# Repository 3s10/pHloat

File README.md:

# pHloat pH Monitoring System

A complete ESP32-based pH monitoring system for brewery fermentation, designed to work alongside Tilt Hydrometers and integrate with Google Sheets.

## System Overview

The pHloat system consists of two components:

1. **pHloat pH Sensor** (ESP32-S3) - Battery-powered sensor that reads pH every minute
2. **pHloat Relay** (ESP32) - Central hub that receives data, calibrates sensors, and uploads to Google Sheets

## Features

- ✅ 1-minute reading intervals with deep sleep for battery efficiency
- ✅ ESP-NOW wireless communication (no WiFi needed for sensors)
- ✅ Web-based configuration and calibration
- ✅ 3-point pH calibration (pH 4, 7, 10)
- ✅ Multiple sensor support (up to 10 sensors)
- ✅ Google Sheets integration with Tilt data matching
- ✅ Local data storage with download capability
- ✅ Storage management with alerts
- ✅ Real-time NTP time synchronization

## Hardware Requirements

### pHloat pH Sensor (per sensor)
- ESP32-S3 development board
- Atlas Scientific pH OEM Circuit (I²C mode)
- Atlas Scientific pH probe
- BNC connector
- Battery (LiPo 3.7V recommended, 2000mAh+ for ~60 days)
- Battery charging circuit (optional but recommended)
- Waterproof enclosure

### pHloat Relay (one per brewery)
- ESP32 development board (any variant)
- USB power supply (always-on)
- Optional: SD card module for extended storage

## Wiring Diagrams

### pH Sensor Wiring

```
ESP32-S3              Atlas Scientific pH OEM
=========             =======================
GPIO 8 (SDA)  ------>  SDA
GPIO 9 (SCL)  ------>  SCL
3.3V          ------>  VCC
GND           ------>  GND

Atlas Scientific pH OEM    pH Probe
========================   =========
PRB (BNC connector) -----> pH Probe (BNC)
```

**Important Notes:**
- The Atlas Scientific pH OEM operates at 3.3V (perfect for ESP32)
- Use I²C mode (default on pH OEM)
- Keep I²C wires as short as possible for reliability
- The pH probe MUST be kept hydrated - store in storage solution when not in use

### Power Considerations

**pH Sensor (Battery-Powered):**
- Deep sleep current: ~10µA
- Active current: ~50mA for ~1 second
- Average: ~0.8mA
- 2000mAh battery = ~104 days runtime (1 reading/minute)

**Relay (Wall-Powered):**
- Continuous operation via USB
- Current draw: ~150mA

## Software Setup

### 1. Arduino IDE Configuration

1. Install Arduino IDE (version 2.0+)
2. Add ESP32 board support:
   - Go to File → Preferences
   - Add to "Additional Board Manager URLs": 
     ```
     https://raw.githubusercontent.com/espressif/arduino-esp32/gh-pages/package_esp32_index.json
     ```
   - Go to Tools → Board → Board Manager
   - Search for "esp32" and install "esp32 by Espressif Systems"

3. Install required libraries:
   - Open Arduino IDE
   - Go to Tools → Manage Libraries
   - Search and install:
     - **ArduinoJson** by Benoit Blanchon (version 6.21.0 or higher)
     - This is required for JSON parsing in the web interface
   
4. IMPORTANT - Atlas Scientific I2C Communication:
   - The code uses direct I2C Wire library commands
   - No separate Atlas library needed
   - Commands are sent via Wire.write() following Atlas protocol

### 2. Upload pH Sensor Sketch

1. Open `pHloat_Sensor/pHloat_Sensor.ino`
2. Select board: Tools → Board → ESP32S3 Dev Module
3. Configure board settings:
   - USB CDC On Boot: Enabled
   - Flash Size: 4MB (or your board's size)
   - Partition Scheme: Default
4. Connect ESP32-S3 via USB
5. Select correct COM port
6. Click Upload

### 3. Upload Relay Sketch

1. Open `pHloat_Relay/pHloat_Relay.ino`
2. **IMPORTANT:** Make sure `pHloat_Relay_WebUI.ino` is in the same folder
3. Select board: Tools → Board → ESP32 Dev Module (or your specific board)
4. Connect ESP32 via USB
5. Select correct COM port
6. Click Upload

### 4. Initial Configuration

#### Configure pH Sensor:

1. Power on the pH sensor while holding the BOOT button (GPIO 0)
2. Connect to WiFi network: `pHloat-XXXXXXXX`
3. Password: check Serial Monitor — a random 16-character password is generated on first boot
4. Open browser to `192.168.4.1`
5. Enter:
   - Device name (e.g., "Fermenter-1")
   - Relay MAC address (get this from relay serial monitor)
6. Save - sensor will reboot and start taking readings

#### Configure Relay:

1. Power on relay
2. Note the MAC address printed in Serial Monitor
3. If WiFi not configured, connect to `pHloat-Relay` AP (password printed to Serial Monitor on first boot)
4. Open browser to `192.168.4.1` (or relay's IP if WiFi configured)
5. Go to Configuration page
6. Enter:
   - WiFi SSID and password
   - NTP server (default: pool.ntp.org)
   - Timezone offset in seconds (e.g., -18000 for EST)
   - Google Sheets URL (optional, see below)
7. Save - relay will reboot and connect to WiFi

## Google Sheets Integration

The relay uses one upload path for **both** Google Apps Script and Tilt Pi. See `integration/UPLOAD_API.md` for the shared JSON contract.

You have **two destination options** for remote upload:

### Option 1: Direct Upload (pHloat Relay → Google Sheets)

Each pHloat Relay uploads directly to Google Sheets using Google Apps Script.

**Pros:**
- Simple setup
- Works anywhere with WiFi
- No additional hardware

**Cons:**
- Each relay needs Google Sheets configured
- Multiple relays = multiple configurations

**Setup:** See "Setup Google Apps Script" section below

### Option 2: Tilt Pi Integration (Recommended for Tilt Users)

If you already have a Raspberry Pi running Tilt Pi, use it as a central hub!

**Pros:**
- ✅ Central hub for both Tilt and pHloat data
- ✅ Better timestamp matching (direct database access)
- ✅ Unified dashboard
- ✅ One Google Sheets configuration
- ✅ Lower power (relays can be eliminated)

**Cons:**
- Requires Raspberry Pi
- Slightly more complex initial setup

**Setup:** See **TILT_PI_INTEGRATION.md** for complete instructions

---

## Setup Google Apps Script (Option 1 - Direct Upload)

1. Create a new Google Sheet for your fermentation data
2. Go to Extensions → Apps Script
3. Delete any existing code
4. Copy and paste the contents of `GoogleAppsScript.js`
5. Save the project (name it "pHloat Logger")
6. Click "Deploy" → "New deployment"
7. Settings:
   - Type: Web app
   - Execute as: Me
   - Who has access: Anyone
8. Click "Deploy"
9. Copy the Web App URL
10. In Apps Script: Project Settings → Script properties → add `PHLOAT_UPLOAD_SECRET` (generate a long random string)
11. Paste the Web App URL into the pHloat Relay configuration
12. Set the same upload token in the Relay **Upload Token** field (or leave blank to reuse the API key)

All relay HTTPS uploads send `X-pHloat-Token` — requests without a matching token are rejected.

### Tilt Integration:

The Google Apps Script automatically searches for Tilt data sheets and matches pH readings by timestamp (±1 minute). 

**Expected Tilt sheet format:**
- Sheet name contains "Tilt" (e.g., "Tilt Red", "Tilt Orange")
- Columns must include: Timestamp, Gravity (or SG), optionally Color

The script will:
1. Create a new sheet for each pH sensor
2. Log pH and temperature readings
3. Find the closest Tilt reading within 1 minute
4. Add Specific Gravity and Tilt Color to the same row

## Calibration Procedure

**IMPORTANT:** Always calibrate pH sensors before first use and periodically during use.

### 3-Point Calibration:

You'll need pH calibration buffers: pH 4.0, 7.0, and 10.0

1. Access the Relay web interface
2. Go to "Calibration" page
3. Select the sensor to calibrate
4. Follow the procedure:
   
   **Step 1: pH 7.0 (mid-point)**
   - Rinse probe with distilled water
   - Place in pH 7.0 buffer
   - Wait 2-3 minutes for stable reading
   - Note the raw pH reading from sensor data
   - Enter in "pH 7.0 Buffer Reading" field
   
   **Step 2: pH 4.0 (low point)**
   - Rinse probe thoroughly
   - Place in pH 4.0 buffer
   - Wait 2-3 minutes
   - Note the reading
   - Enter in "pH 4.0 Buffer Reading" field
   
   **Step 3: pH 10.0 (high point)**
   - Rinse probe thoroughly
   - Place in pH 10.0 buffer
   - Wait 2-3 minutes
   - Note the reading
   - Enter in "pH 10.0 Buffer Reading" field

5. Click "Save Calibration"

**Calibration Tips:**
- Always start with pH 7, then pH 4, then pH 10
- Rinse probe between each buffer
- Wait for readings to stabilize
- Calibrate at the temperature you'll be measuring (or use temperature compensation)
- Re-calibrate every 30 days or when you notice drift

## Usage

### Normal Operation:

1. **Sensors:**
   - Wake every 60 seconds
   - Take pH and temperature reading
   - Send via ESP-NOW to relay
   - Return to deep sleep
   - Battery indicator: LED flashes once per reading

2. **Relay:**
   - Receives data from all sensors
   - Applies calibration corrections
   - Saves data locally
   - Uploads to Google Sheets (if enabled)
   - Provides web interface for monitoring

### Monitoring Data:

**Via Web Interface:**
1. Connect to relay's IP address
2. Click "Data Review"
3. View all data files
4. Download CSV files for analysis
5. Delete old files to free space

**Via Google Sheets:**
1. Open your fermentation Google Sheet
2. Each sensor has its own sheet
3. Data includes: Timestamp, pH, Temperature, Specific Gravity (from Tilt), Tilt Color
4. Use built-in Google Sheets features for charts and analysis

### Storage Management:

- The relay monitors storage space
- Reserves 512KB for current logging
- Alerts appear when free space drops below 512KB
- Critical alert at 100KB free
- Manually delete old files through web interface

## Troubleshooting

### pH Sensor Not Sending Data:

1. Check MAC address is correct in sensor config
2. Verify relay is powered on
3. Check distance between sensor and relay (ESP-NOW range ~100m)
4. View serial monitor for error messages

### Incorrect pH Readings:

1. Check calibration is current (within 30 days)
2. Verify probe is properly hydrated
3. Check probe is not fouled (clean with probe cleaner)
4. Ensure probe junction is not clogged
5. Check temperature compensation is working

### WiFi Connection Issues:

1. Verify SSID and password are correct
2. Check WiFi signal strength at relay location
3. Ensure router allows 2.4GHz connections (ESP32 doesn't support 5GHz)
4. Try rebooting router

### Google Sheets Not Updating:

1. Verify deployment URL is correct
2. Check Apps Script permissions are set correctly
3. View Apps Script logs (View → Logs in Apps Script editor)
4. Ensure relay has internet connection
5. Check that "Enable Google Sheets Upload" is checked in relay config

### Battery Life Issues:

1. Verify deep sleep is working (serial monitor shows "Going to sleep")
2. Check battery capacity (should be 2000mAh minimum)
3. Verify no LEDs are staying on during sleep
4. Consider reducing reading frequency if needed (edit SLEEP_DURATION in code)

## Advanced Configuration

### Changing Reading Interval:

Edit `pHloat_Sensor.ino`:
```cpp
#define SLEEP_DURATION 60  // Change to desired seconds (e.g., 300 = 5 minutes)
```

### Adding More Sensors:

Edit `pHloat_Relay.ino`:
```cpp
#define MAX_SENSORS 10  // Increase if you need more than 10 sensors
```

### Custom I²C Pins:

Edit `pHloat_Sensor.ino`:
```cpp
#define I2C_SDA 8  // Change to your preferred GPIO
#define I2C_SCL 9  // Change to your preferred GPIO
```

## pH Probe Care

**Daily:**
- Ensure probe is submerged in fermentation or storage solution
- Never let probe dry out

**Weekly:**
- Rinse with distilled water
- Check for buildup on glass bulb

**Monthly:**
- Clean with pH probe cleaning solution
- Re-calibrate
- Check electrolyte level (if refillable probe)

**Storage:**
- Store in pH 4.0 buffer or storage solution
- NEVER store in distilled water (damages probe)
- Keep protective cap on when not in use

## Bill of Materials (BOM)

### Per pH Sensor:
| Item | Quantity | Approx. Cost | Notes |
|------|----------|--------------|-------|
| ESP32-S3 Dev Board | 1 | $8-15 | Any ESP32-S3 with battery charging |
| Atlas Scientific pH OEM | 1 | $60 | From Atlas Scientific |
| pH Probe (BNC) | 1 | $50-100 | Atlas or third-party |
| LiPo Battery 3.7V 2000mAh | 1 | $8-12 | JST connector |
| Waterproof enclosure | 1 | $10-15 | IP67 rated |
| Misc (wire, connectors) | - | $5 | - |
| **Total per sensor** | | **~$140-200** | |

### For Relay:
| Item | Quantity | Approx. Cost | Notes |
|------|----------|--------------|-------|
| ESP32 Dev Board | 1 | $6-10 | Any ESP32 variant |
| USB Power Supply | 1 | $5 | 5V 1A minimum |
| Enclosure (optional) | 1 | $8 | - |
| **Total for relay** | | **~$15-25** | |

## License

This project is released under the MIT License. Feel free to modify and use for personal or commercial applications.

## Credits

Created for homebrewers and craft brewers who want to monitor pH during fermentation alongside their Tilt Hydrometers.

## Support

For issues, questions, or contributions, please open an issue on the project repository.

## Version History

- v1.0.0 - Initial release
  - ESP-NOW communication
  - Web UI for configuration and calibration
  - Google Sheets integration
  - Tilt data matching
  - Local storage management
  - Deep sleep for battery efficiency

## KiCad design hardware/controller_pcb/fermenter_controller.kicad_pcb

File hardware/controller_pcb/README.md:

# Fermenter controller PCB, rev A

**Status (2026-11-15): board generated and DRC-checked in KiCad 10.0.8 (0 errors, 0 unconnected; remaining warnings are silkscreen). Schematic generated; its netlist matches the board (13 nets, 58 pins). Top render viewed; the schematic drawing has not been looked at by eye. Not fabricated, not assembled, not tested.**

Carrier for a XIAO ESP32-S3 that drives two 12 V DC pumps and reads up to four DS18B20 probes. 92 x 62 mm, 2 layers. Firmware: `esphome/fermenter_controller.yaml`. Enclosure: `../controller_enclosure/`.

## Files

| File | What it is |
|---|---|
| `gen_pcb.py` | Source of truth: parts, netlist, placement, routing. Regenerates the board. |
| `fermenter_controller.kicad_pro` | KiCad project. Open this. |
| `gen_sch.py` | Builds the schematic from the same netlist table, reusing the sensor board's generator. |
| `fermenter_controller.kicad_sch`, `fermenter_controller_schematic.pdf` | Generated schematic and its PDF. |
| `phloat.kicad_sym`, `sym-lib-table`, `fp-lib-table` | Project symbol library and the tables that point KiCad at it. |
| `fermenter_controller.kicad_pcb` | Generated board. Hand edits are lost on regeneration. |
| `fab/` | Gerbers, drill files, pick-and-place CSV. |
| `render_top.png`, `render_bottom.png` | 3D renders. |

```
"C:\Program Files\KiCad\10.0\bin\python.exe" gen_pcb.py
"C:\Program Files\KiCad\10.0\bin\python.exe" gen_sch.py
"C:\Program Files\KiCad\10.0\bin\kicad-cli.exe" pcb drc --severity-all fermenter_controller.kicad_pcb
"C:\Program Files\KiCad\10.0\bin\kicad-cli.exe" sch erc --severity-all fermenter_controller.kicad_sch
"C:\Program Files\KiCad\10.0\bin\kicad-cli.exe" sch export netlist --format kicadsexpr -o sch.net fermenter_controller.kicad_sch
"C:\Program Files\KiCad\10.0\bin\python.exe" ..\phloat_sensor_pcb\check_netlist.py sch.net .
```

Expected ERC result: two `power_pin_not_driven` errors on U2 (its supply and ground pins), because the supply arrives through a terminal block and the drawing has no power-flag symbols; and two `lib_symbol_mismatch` warnings from flattened library symbols. Expected netlist check: `netlist OK: 13 nets, 58 pins match gen_pcb.NETS`.

The schematic connects pins with named labels, not drawn wires, and has not been looked at by eye; expect overlapping labels.

## Connections

| Terminal | Pins (as printed on the board) | Use |
|---|---|---|
| J1 | + / - | 12 V DC supply |
| J2 | + / - | Cooling pump |
| J3 | + / - | Warming pump |
| J4-J7 | GND, DQ, 3V3 | DS18B20 probes: coolant, warm fluid, ambient, thermowell (all on one bus; any probe works in any terminal) |

| XIAO pin | GPIO | Net |
|---|---|---|
| D3 | 4 | DQ (1-Wire, 4.7k pull-up R5) |
| D4 | 5 | Cooling pump PWM |
| D5 | 6 | Warming pump PWM |
| 5V | - | From the on-board regulator through D3 |

## Circuit

- **Supply:** J1 -> 5x20 mm fuse F1 -> fused 12 V rail. D4 (TVS) clamps spikes and, on a reversed supply, conducts and blows the fuse. C1 is bulk capacitance for the pumps.
- **Logic power:** U2 (Traco TSR 1-2450 switching regulator, drop-in SIP-3) makes 5 V. D3 feeds the XIAO's 5V pin and stops USB back-feeding the rail, so USB can be plugged in with 12 V present.
- **Pumps:** low-side switched by Q1/Q2 (AO3400A). R1/R2 are 100 ohm gate resistors. **R3/R4 (10k) pull the gates low, so both pumps are off whenever the XIAO is booting, resetting, unpowered or absent.** D1/D2 are flyback diodes.

## Limits

- **12 V pumps only.** The FETs are 30 V parts and the TVS is sized for 12 V. Do not use a 24 V supply.
- **About 2 A per pump.** Set by the SOT-23 FETs and 1.5 mm switch traces. Fuse F1 at 5 A or less.
- The pumps must tolerate PWM on their supply (brushed DC pumps do; many brushless ones don't).

## BOM

| Ref | Part |
|---|---|
| U1 | Seeed XIAO ESP32-S3 (soldered flat; not Plus or Sense) |
| U2 | Traco TSR 1-2450 |
| Q1, Q2 | AO3400A (SOT-23 N-MOSFET, pinout G-S-D = 1-2-3) |
| D1, D2 | SS34 (SMA Schottky) |
| D3 | B5819W (SOD-123 Schottky) |
| D4 | SMBJ15A (SMB TVS, unidirectional, cathode to +) |
| F1 | 5x20 mm fuse clips (Littelfuse 111 series) + fuse |
| C1 | 220 uF 25 V radial, 8 mm, 3.5 mm pitch |
| C3 | 22 uF 10 V 0805 |
| R1, R2 | 100 ohm 0805 |
| R3, R4 | 10k 0805 |
| R5 | 4.7k 0805 |
| J1-J3 | Phoenix MKDS 1,5/2-5,08 |
| J4-J7 | Phoenix PT 1,5/3-3,5-H |
| H1-H4 | M3 holes |

## Check before ordering

1. **Diode polarity.** D1, D2, D4: cathode (pad 1) is on the +12 V side in the netlist. Confirm against the silkscreen when placing; a reversed flyback diode is a dead short across the supply.
2. **XIAO footprint** is Seeed's (CC-BY-SA-4.0). One GND via sits under the module at (85.3, 26.4) mm from the board's top-left: order tented vias.
3. **Terminal block orientation.** Wire entries should face the board edges (probes top, power left, pumps bottom). Check the first board before soldering all seven.
4. **TSR 1-2450 pinout** is 1 = Vin, 2 = GND, 3 = Vout as in the KiCad footprint; confirm on the part you buy.

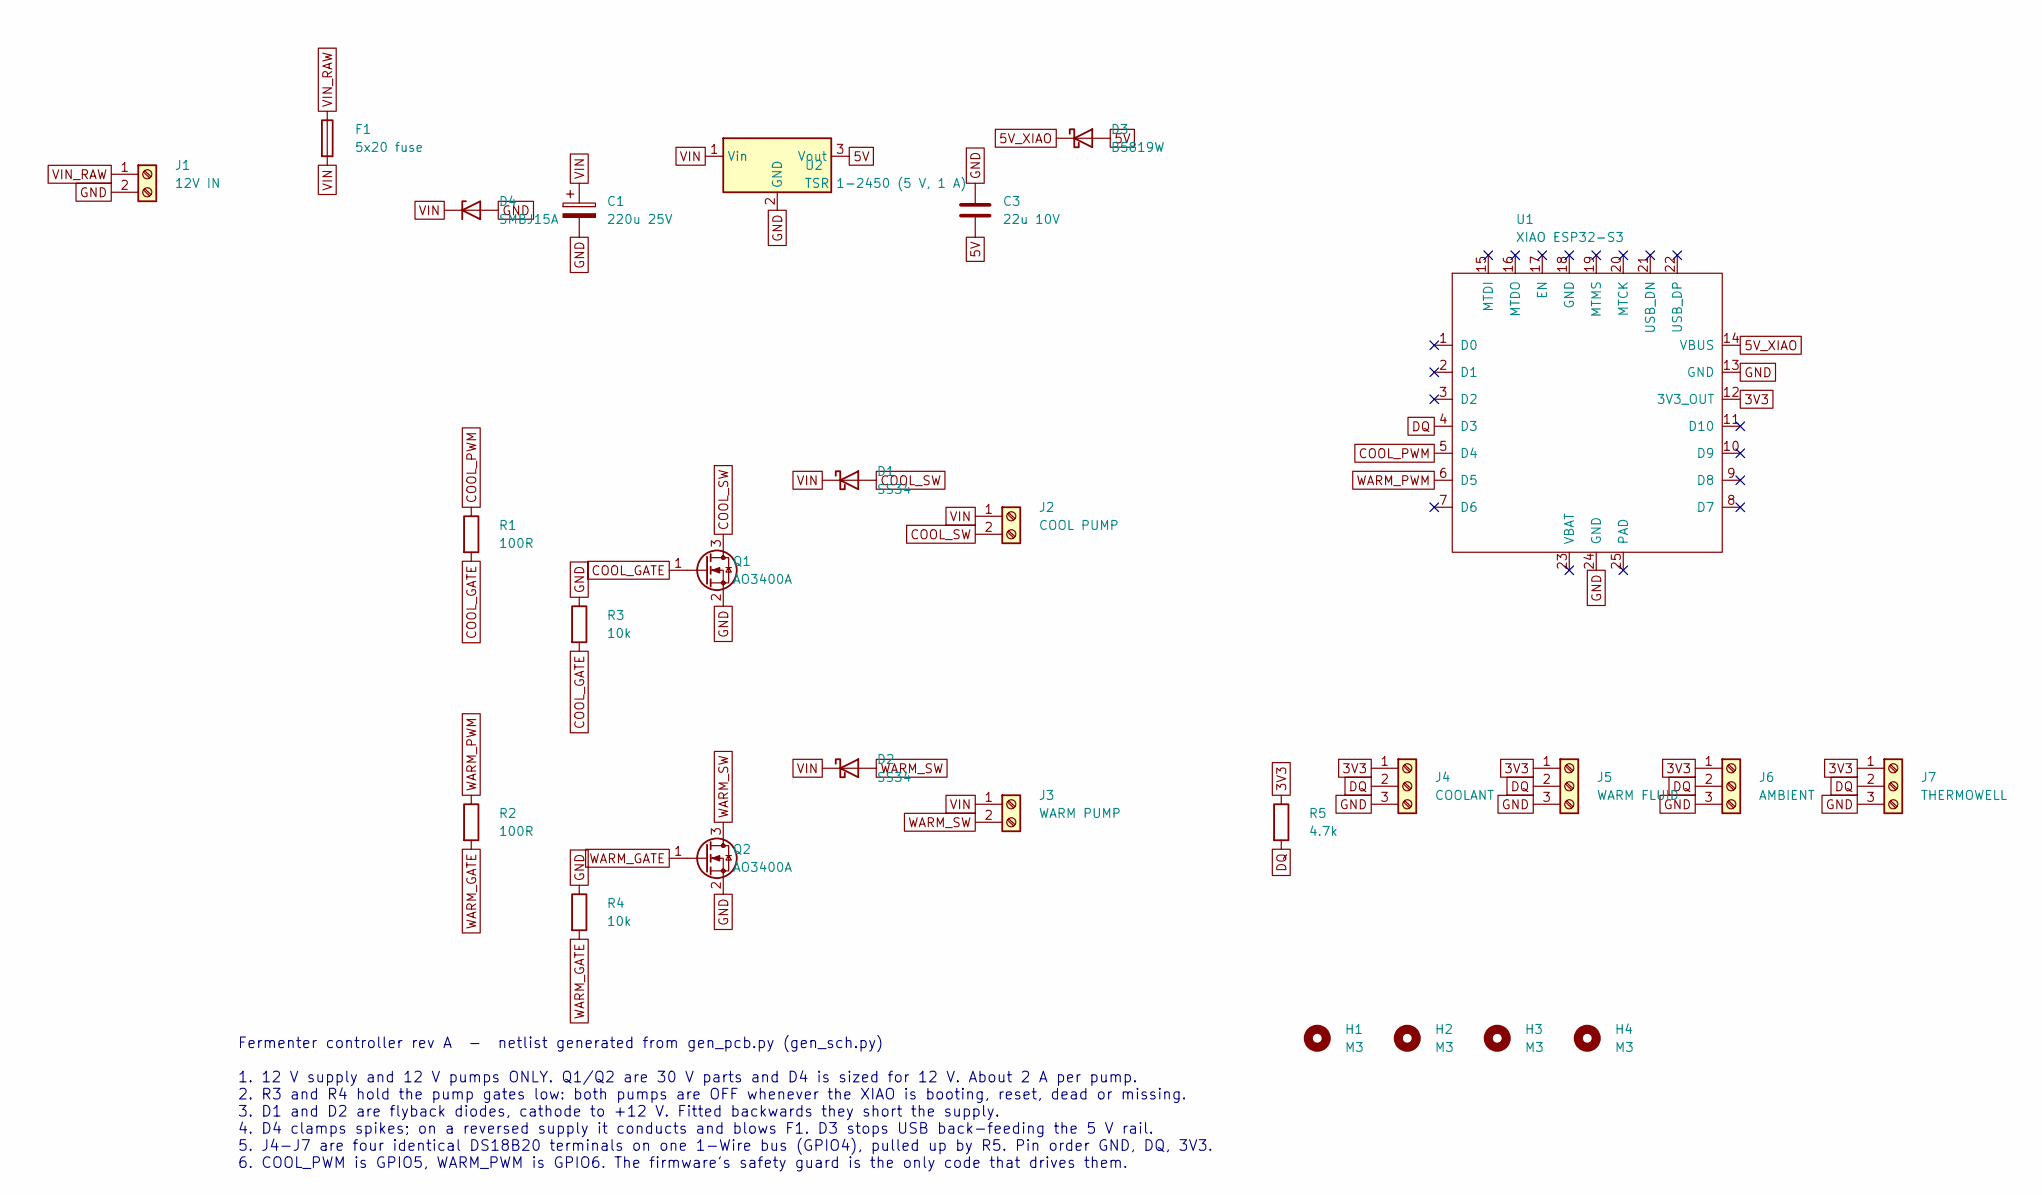
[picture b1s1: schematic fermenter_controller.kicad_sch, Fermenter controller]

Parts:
C1: 220u 25V; CP_Radial_D8.0mm_P3.50mm
C3: 22u 10V; C_0805_2012Metric_Pad1.18x1.45mm_HandSolder
D1, D2: SS34; D_SMA
D3: B5819W; D_SOD-123
D4: SMBJ15A; D_SMB
F1: 5x20 fuse; Fuseholder_Clip-5x20mm_Littelfuse_111_Inline_P20.00x5.00mm_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
H1, H2, H3, H4: M3; MountingHole_3.2mm_M3
J1: 12V IN; TerminalBlock_Phoenix_MKDS-1,5-2-5.08_1x02_P5.08mm_Horizont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
J2: COOL PUMP; TerminalBlock_Phoenix_MKDS-1,5-2-5.08_1x02_P5.08mm_Horizont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
J3: WARM PUMP; TerminalBlock_Phoenix_MKDS-1,5-2-5.08_1x02_P5.08mm_Horizont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
J4: COOLANT; TerminalBlock_Phoenix_PT-1,5-3-3.5-H_1x03_P3.50mm_Horizontal
J5: WARM FLUID; TerminalBlock_Phoenix_PT-1,5-3-3.5-H_1x03_P3.50mm_Horizontal
J6: AMBIENT; TerminalBlock_Phoenix_PT-1,5-3-3.5-H_1x03_P3.50mm_Horizontal
J7: THERMOWELL; TerminalBlock_Phoenix_PT-1,5-3-3.5-H_1x03_P3.50mm_Horizontal
Q1, Q2: AO3400A; SOT-23
R1, R2: 100R; R_0805_2012Metric_Pad1.20x1.40mm_HandSolder
R3, R4: 10k; R_0805_2012Metric_Pad1.20x1.40mm_HandSolder
R5: 4.7k; R_0805_2012Metric_Pad1.20x1.40mm_HandSolder
U1: XIAO ESP32-S3; XIAO-ESP32-S3-SMD
U2: TSR 1-2450 (5 V, 1 A); Converter_DCDC_TRACO_TSR-1_THT

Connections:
3V3: J4.1, J5.1, J6.1, J7.1, R5.1, U1.12 (3V3_OUT)
5V: C3.2, D3.2 (A), U2.3 (Vout)
5V_XIAO: D3.1 (K), U1.14 (VBUS)
COOL_GATE: Q1.1 (G), R1.2, R3.2
COOL_PWM: R1.1, U1.5 (D4)
COOL_SW: D1.2 (A), J2.2, Q1.3 (D)
DQ: J4.2, J5.2, J6.2, J7.2, R5.2, U1.4 (D3)
GND: C1.2, C3.1, D4.2 (A), J1.2, J4.3, J5.3, J6.3, J7.3, Q1.2 (S), Q2.2 (S), R3.1, R4.1, U1.13 (GND), U1.24 (GND), U2.2 (GND)
VIN: C1.1, D1.1 (K), D2.1 (K), D4.1 (K), F1.2, J2.1, J3.1, U2.1 (Vin)
VIN_RAW: F1.1, J1.1
WARM_GATE: Q2.1 (G), R2.2, R4.2
WARM_PWM: R2.1, U1.6 (D5)
WARM_SW: D2.2 (A), J3.2, Q2.3 (D)

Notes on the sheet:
Fermenter controller rev A - netlist generated from gen_pcb.py (gen_sch.py) 1. 12 V supply and 12 V pumps ONLY. Q1/Q2 are 30 V parts and D4 is sized for 12 V. About 2 A per pump. 2. R3 and R4 hold the pump gates low: both pumps are OFF whenever the XIAO is booting, reset, dead or missing. 3. D1 and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

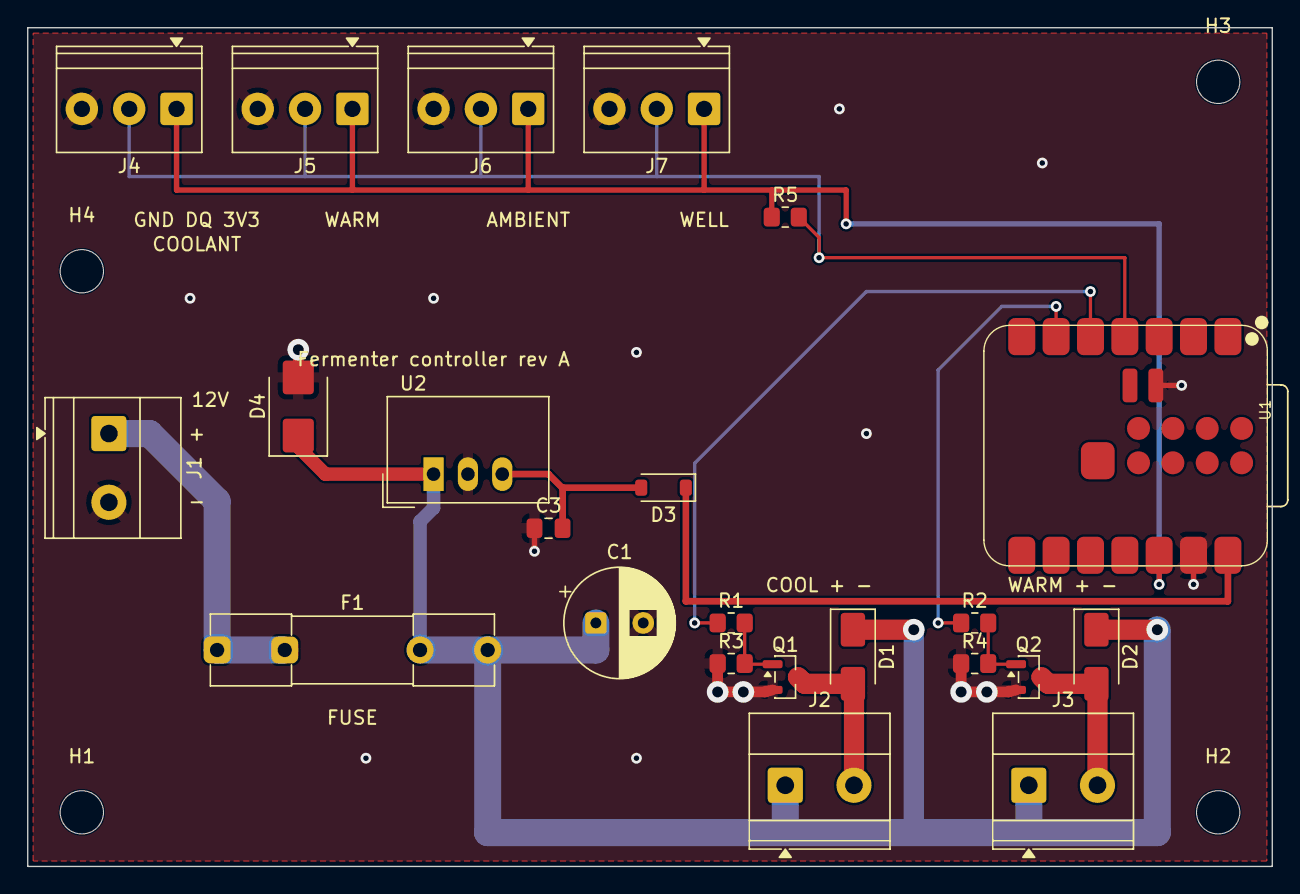
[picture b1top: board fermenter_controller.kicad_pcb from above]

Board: 2 copper layers, 92.0 x 62.0 mm, 27 parts (0 on the bottom side), 13 nets.

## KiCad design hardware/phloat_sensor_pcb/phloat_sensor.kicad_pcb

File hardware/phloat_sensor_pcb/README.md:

# pHloat sensor PCB, rev A

**Status (2026-11-14): generated and DRC-checked in KiCad 10.0.8. Not fabricated, not assembled, not tested.**

External pH node: XIAO ESP32-S3 + Atlas pH OEM + SMA probe jack on the front, 18650 holder on the back. 118 x 32 mm, 2 layers.

## Files

| File | What it is |
|---|---|
| `gen_pcb.py` | Source of truth: parts, netlist, placement, routing. Regenerates the board. |
| `phloat_sensor.kicad_pro` | KiCad project. Open this. |
| `gen_sch.py` | Builds the schematic from the same netlist table, using labels instead of drawn wires. |
| `phloat_sensor.kicad_sch`, `phloat_sensor_schematic.pdf` | Generated schematic and its PDF. |
| `check_netlist.py` | Fails if the schematic netlist and `gen_pcb.NETS` ever differ. |
| `phloat_sensor.kicad_pcb` | Generated board. Open in KiCad to inspect; hand edits are lost on regeneration. |
| `phloat.kicad_sym`, `seeed_xiao.kicad_sym` | Project symbols (ours + Seeed's XIAO, CC-BY-SA-4.0) and the Seeed source library. |
| `phloat.pretty/` | `Atlas_pH_OEM` (ours) and `XIAO-ESP32-S3-SMD` (Seeed, CC-BY-SA-4.0, from github.com/Seeed-Studio/OPL_Kicad_Library). |
| `fab/` | Gerbers, drill files, pick-and-place CSV. |
| `render_top.png`, `render_bottom.png` | 3D renders. |

The `NETS` table in `gen_pcb.py` is the single source for both the schematic and the board.

## Rebuild and check

```
"C:\Program Files\KiCad\10.0\bin\python.exe" gen_pcb.py
"C:\Program Files\KiCad\10.0\bin\python.exe" gen_sch.py
"C:\Program Files\KiCad\10.0\bin\kicad-cli.exe" pcb drc --severity-all phloat_sensor.kicad_pcb
"C:\Program Files\KiCad\10.0\bin\kicad-cli.exe" sch erc --severity-all phloat_sensor.kicad_sch
"C:\Program Files\KiCad\10.0\bin\kicad-cli.exe" sch export netlist --format kicadsexpr -o sch.net phloat_sensor.kicad_sch
"C:\Program Files\KiCad\10.0\bin\python.exe" check_netlist.py sch.net
```

Expected DRC result: 0 unconnected items; 5 `copper_edge_clearance` errors, all on J1 (edge-mount SMA pads reach the board edge by design); the rest are silkscreen warnings.

Expected ERC result: one `lib_symbol_mismatch` warning on Q1 (the embedded AO3401A symbol is a flattened copy).

Expected parity result (`pcb drc --schematic-parity`): 22 `net_conflict` warnings, all for deliberately unconnected pads that the schematic names `unconnected-...`.

The schematic drawing has not been looked at by eye; expect overlapping labels that need tidying in eeschema.

## Pin map (firmware must match)

| XIAO pin | GPIO | Net | Purpose |
|---|---|---|---|
| D3 | 4 | SDA | I2C data to OEM (0x65) |
| D4 | 5 | PH_PWR | Drive HIGH to power the OEM and the I2C pull-ups; float/LOW in deep sleep |
| D5 | 6 | SCL | I2C clock |
| D8 | 7 | BAT_SENSE | Cell voltage / 2 (470k/470k, 100n) |
| BAT+ pad (underside) | - | VBAT | Cell + after reverse-polarity FET |

`Wire.begin(4, 6)`. These are not the XIAO default I2C pins; they were chosen so the board routes without crossings.

## Circuit

- **Power:** 18650 + -> Q1 (P-FET, gate to GND: blocks a reversed cell) -> XIAO BAT+ pad. The XIAO regulator makes 3.3 V. No charging path is intended; swap cells.
- **OEM power gating:** OEM VCC, both 4.7k pull-ups, C1 and C2 hang off GPIO5. R5 (100k) holds the rail low when the GPIO floats. OEM draws about 3.5 mA at 3.3 V (datasheet V4.7 p6).
- **Probe:** SMA centre -> OEM pin 4 by a 7.5 mm, 0.4 mm trace. SMA shell -> OEM pin 5 (`PRBG`). `PRBG` has its own pour on both layers around the probe trace and is never connected to `GND` (datasheet p33-34).
- **OEM pins 2, 9, 10 (NC) and 7 (INT)** are left floating as the datasheet requires. No vias under the module.

## BOM

| Ref | Part | Notes |
|---|---|---|
| U1 | Seeed XIAO ESP32-S3 | Soldered flat (castellations + underside BAT pads). Not the "Plus" or "Sense". |
| U2 | Atlas Scientific pH OEM | Reflow or hot air. Remove all flux afterwards (datasheet p4). |
| J1 | Amphenol 132289 SMA edge-mount jack | For 1.6 mm board |
| BT1 | Keystone 1042 18650 holder | Back side |
| Q1 | AO3401A (SOT-23 P-MOSFET) | Any logic-level P-FET, Vgs(th) under 1.5 V, pinout G-S-D = 1-2-3 |
| R1, R2 | 4.7k 0805 | I2C pull-ups |
| R3, R4 | 470k 0805 | Battery divider |
| R5 | 100k 0805 | PH_PWR pull-down |
| C1, C3 | 100n 0805 | |
| C2 | 1u 0805 | |
| H1-H4 | M2.5 holes | |

Off-board: Atlas Lab Grade pH probe (ENV-40-pH, male SMA, $99.99) and Atlas Tri-Clamp Probe Pipe Fitting (1.5", NSF-51, $34.99). Prices as listed on atlas-scientific.com on 2026-11-14.

## Check before ordering boards

1. **OEM footprint.** Print the board 1:1 and lay the module on it. Pad pitch is 2.25 mm (Atlas DXF averages 2.25; datasheet says 2.3). Confirm pin 1 (SDA) is at the silkscreen dot, top-left with the probe pins facing the SMA jack.
2. **XIAO BAT pads.** Confirm the two underside battery pads on your XIAO line up with pads 23/24 of the Seeed footprint.
3. **Protected 18650 length.** The Keystone 1042 is sized for bare cells; many protected cells (67-69 mm) will not fit. Firmware must stop transmitting below about 3.2 V because there is no hardware under-voltage cut-off.
4. **Under-module vias.** One GND via sits under the XIAO at (111.3, 11.55) mm from the board's top-left corner. Order tented vias.
5. **Seeed footprint licence** is CC-BY-SA-4.0. Fine for prototypes; check the terms before shipping a commercial design that includes it.

## Not on this board

- No temperature sensor: beer temperature comes from the Tilt over BLE.
- No galvanic isolation: the node is battery powered and floating. Do not take readings with USB plugged into a grounded computer and expect them to be accurate.
- No conformal-coat keep-outs are marked. Mask J1, the 18650 contacts and the XIAO USB-C port before coating. If you coat the OEM module, use clear coating only (datasheet p37).

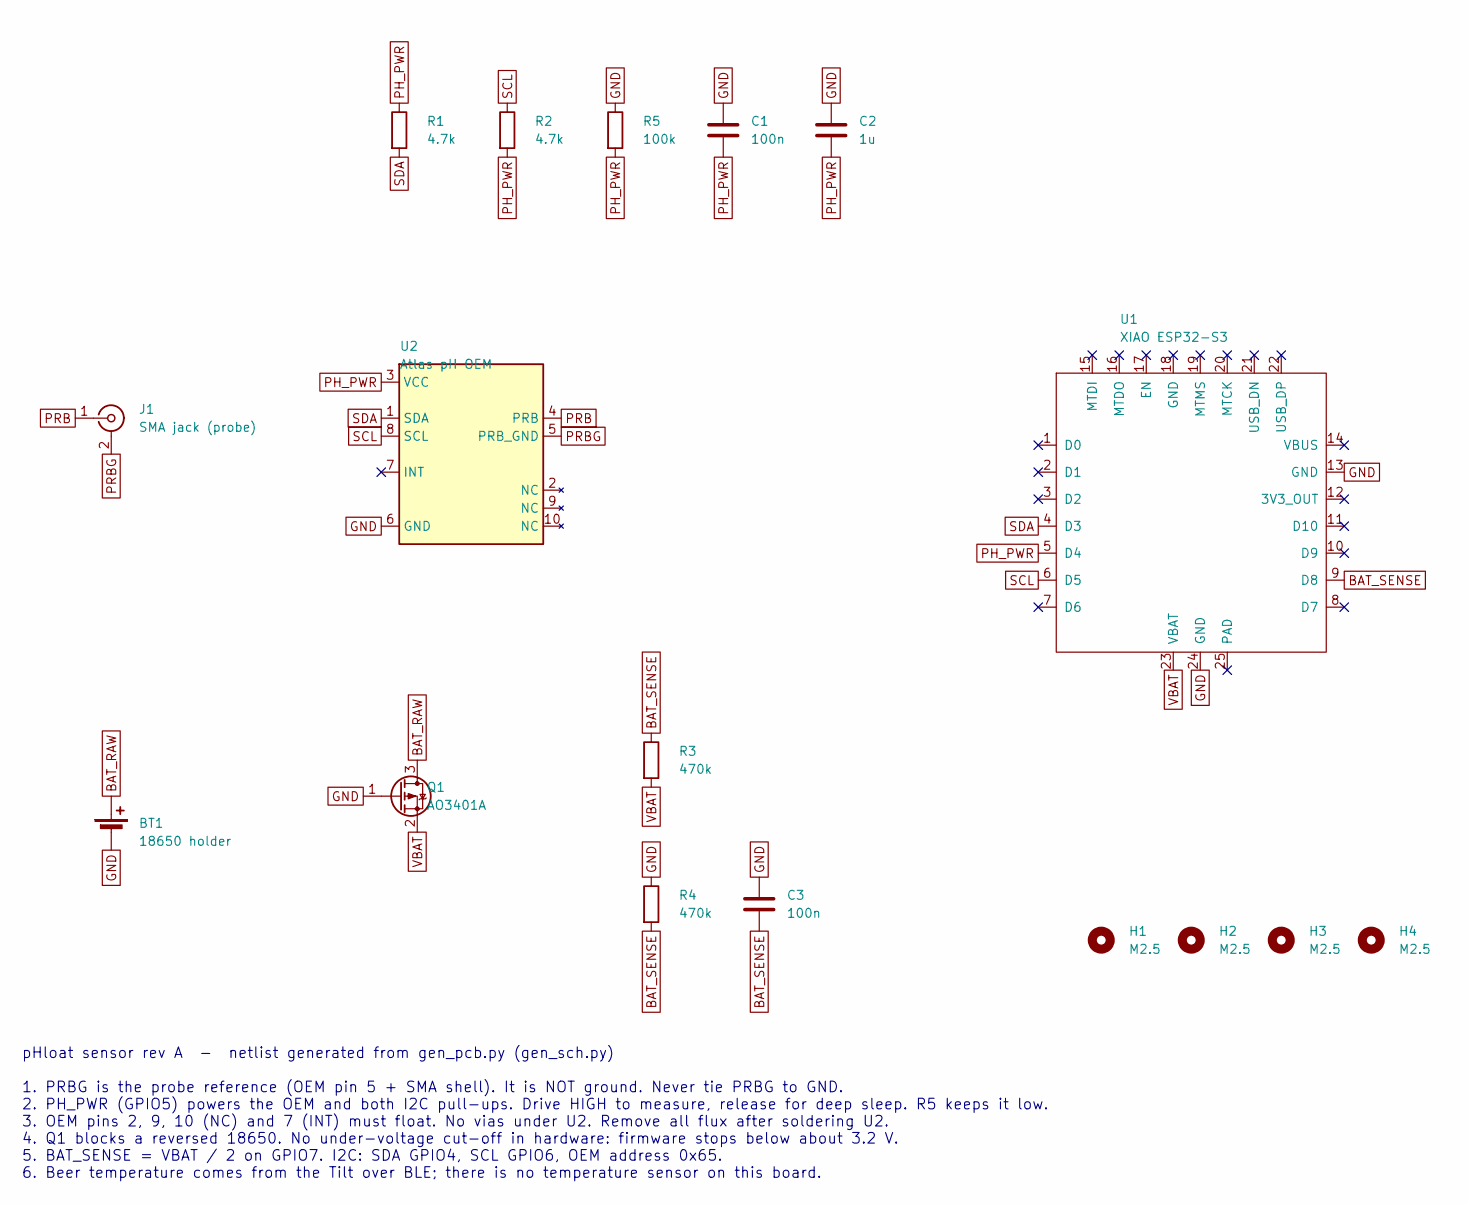
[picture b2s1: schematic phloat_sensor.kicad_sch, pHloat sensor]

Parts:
BT1: 18650 holder; BatteryHolder_Keystone_1042_1x18650
C1, C3: 100n; C_0805_2012Metric_Pad1.18x1.45mm_HandSolder
C2: 1u; C_0805_2012Metric_Pad1.18x1.45mm_HandSolder
H1, H2, H3, H4: M2.5; MountingHole_2.7mm_M2.5
J1: SMA jack (probe); SMA_Amphenol_132289_EdgeMount
Q1: AO3401A; SOT-23
R1, R2: 4.7k; R_0805_2012Metric_Pad1.20x1.40mm_HandSolder
R3, R4: 470k; R_0805_2012Metric_Pad1.20x1.40mm_HandSolder
R5: 100k; R_0805_2012Metric_Pad1.20x1.40mm_HandSolder
U1: XIAO ESP32-S3; XIAO-ESP32-S3-SMD
U2: Atlas pH OEM; Atlas_pH_OEM

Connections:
BAT_RAW: BT1.1 (+), Q1.3 (D)
BAT_SENSE: C3.2, R3.1, R4.2, U1.9 (D8)
GND: BT1.2 (-), C1.1, C2.1, C3.1, Q1.1 (G), R4.1, R5.1, U1.13 (GND), U1.24 (GND), U2.6 (GND)
PH_PWR: C1.2, C2.2, R1.1, R2.2, R5.2, U1.5 (D4), U2.3 (VCC)
PRB: J1.1 (In), U2.4 (PRB)
PRBG: J1.2 (Ext), U2.5 (PRB_GND)
SCL: R2.1, U1.6 (D5), U2.8 (SCL)
SDA: R1.2, U1.4 (D3), U2.1 (SDA)
VBAT: Q1.2 (S), R3.2, U1.23 (VBAT)

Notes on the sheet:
pHloat sensor rev A - netlist generated from gen_pcb.py (gen_sch.py) 1. PRBG is the probe reference (OEM pin 5 + SMA shell). It is NOT ground. Never tie PRBG to GND. 2. PH_PWR (GPIO5) powers the OEM and both I2C pull-ups. Drive HIGH to measure, release for deep sleep. R5 keeps it low. 3. OEM pins 2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

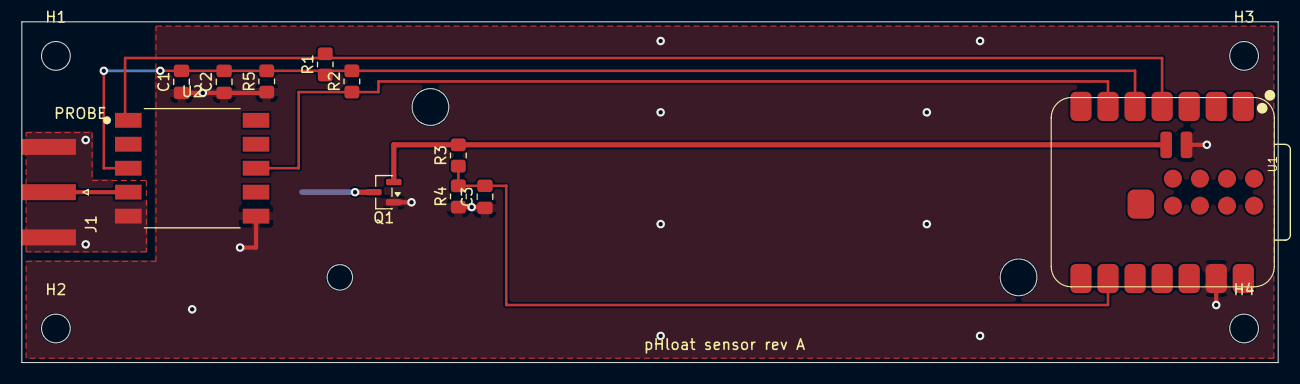
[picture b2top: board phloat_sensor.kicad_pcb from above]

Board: 2 copper layers, 118.0 x 32.0 mm, 17 parts (1 on the bottom side), 9 nets.

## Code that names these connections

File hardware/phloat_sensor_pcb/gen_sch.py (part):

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			(pin input line (at -12.7 2.54 0) (length 2.54) (name "SCL" (effects (font (size 1.27 1.27)))) (number "8" (effects (font (size 1.27 1.27)))))
			(pin output line (at -12.7 -2.54 0) (length 2.54) (name "INT" (effects (font (size 1.27 1.27)))) (number "7" (effects (font (size 1.27 1.27)))))
			(pin passive line (at -12.7 -10.16 0) (length 2.54) (name "GND" (effects (font (size 1.27 1.27)))) (number "6" (effects (font (size 1.27 1.27)))))
			(pin passive line (at 12.7 5.08 180) (length 2.54) (name "PRB" (effects (font (size 1.27 1.27)))) (number "4" (effects (font (size 1.27 1.27)))))
			(pin passive line (at 12.7 2.54 180) (length 2.54) (name "PRB_GND" (effects (font (size 1.27 1.27)))) (number "5" (effects (font (size 1.27 1.27)))))
			(pin no_connect line (at 12.7 -5.08 180) (length 2.54) (name "NC" (effects (font (size 1.27 1.27)))) (number "2" (effects (font (size 1.27 1.27)))))
			(pin no_connect line (at 12.7 -7.62 180) (length 2.54) (name "NC" (effects (font (size 1.27 1.27)))) (number "9" (effects (font (size 1.27 1.27)))))
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# Design notes printed on the schematic itself, so the rules travel with the drawing.
NOTES = """pHloat sensor rev A  -  netlist generated from gen_pcb.py (gen_sch.py)

1. PRBG is the probe reference (OEM pin 5 + SMA shell). It is NOT ground. Never tie PRBG to GND.
2. PH_PWR (GPIO5) powers the OEM and both I2C pull-ups. Drive HIGH to measure, release for deep sleep. R5 keeps it low.
3. OEM pins 2, 9, 10 (NC) and 7 (INT) must float. No vias under U2. Remove all flux after soldering U2.
4. Q1 blocks a reversed 18650. No under-voltage cut-off in hardware: firmware stops below about 3.2 V.
5. BAT_SENSE = VBAT / 2 on GPIO7. I2C: SDA GPIO4, SCL GPIO6, OEM address 0x65.
6. Beer temperature comes from the Tilt over BLE; there is no temperature sensor on this board."""


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
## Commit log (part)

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2026-05-19 Initial commit: pHloat backup 2026-05-19
2026-06-10 Harden security, unify upload path, and extract Web UI templates.
    Fix review findings with shared secrets, fail-closed auth, ESP-NOW MAC allowlist, and sanitized device names. Consolidate Google Apps Script and Tilt Pi uploads behind one relay payload and contract,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
